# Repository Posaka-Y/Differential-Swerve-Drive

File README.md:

# Differential Swerve Drive

差動ステアユニット3基で構成する移動機構の、機構・制御・基板・ファームウェアをまとめた開発リポジトリです。

各ユニットはM3508+C620を2組とAMT222A-Vを持ち、ユニット内で差動の操舵・駆動制御を完結します。中央Teensy 4.1が3ユニットを協調制御し、mini PCはUSB-CDC経由でGUI・ログ・キャリブレーション操作を担います。

## 現在の構成

```text
mini PC (GUI / log)
  | USB-CDC
Teensy 4.1 (中央制御・安全I/O)
  |-- CAN1: 差動ステアユニット x3
  |     `-- STM32G474RET6 + C620 x2 + M3508 x2 + AMT222A-V
  |
  `-- CAN3: オドメトリ/IMUノード (unitId=4)
        `-- STM32F405RGT6 + AMT102 x3 + ICM-42688-P
```

- 中央CANとユニット内C620 CANは、いずれもClassic CAN 1 Mbpsの別バス。
- 制御系は中央の24V→5V降圧から`COMM_A / COMM_B / +5V / GND`で分配し、各基板で3.3Vを生成する。
- 確定事項の唯一の正本は[docs/ARCHITECTURE_DECISIONS.md](docs/ARCHITECTURE_DECISIONS.md)。

## まず読むもの

| 目的 | 文書 |
|---|---|
| 文書全体の案内 | [docs/PROJECT_DOCUMENT_INDEX.md](docs/PROJECT_DOCUMENT_INDEX.md) |
| 現在地・次の作業 | [PROGRESS.md](PROGRESS.md) |
| 設計上の確定事項 | [docs/ARCHITECTURE_DECISIONS.md](docs/ARCHITECTURE_DECISIONS.md) |
| 全体構成と責務 | [docs/SYSTEM_ARCHITECTURE.md](docs/SYSTEM_ARCHITECTURE.md) |
| ユニット基板・中央基板・オドメトリ基板 | [docs/electrical/](docs/electrical/) |
| 制御・運動学 | [docs/control/](docs/control/) |
| CAN・ネット名・メッセージ | [docs/communication/COMMUNICATION_NAMING_AND_IDS.md](docs/communication/COMMUNICATION_NAMING_AND_IDS.md) |
| ファームウェア | [firmware/README.md](firmware/README.md) と [firmware/PROGRESS.md](firmware/PROGRESS.md) |
| KiCad基板設計 | [hardware/README.md](hardware/README.md) |

階層化済みの`docs/control/`、`docs/electrical/`、`docs/communication/`などが更新対象です。`docs/`直下の旧メモは履歴として保存しており、更新対象ではありません。

## よく使うコマンド

リポジトリルートで実行します。

```powershell
# STM32G474 ファームウェア
.\firmware\scripts\build.ps1
.\firmware\scripts\flash.ps1

# KiCad設計のERC・PDF・DRC確認
.\tools\kicad\check.ps1
```

ファームウェア用ツールチェーンはスクリプトが自動検出します。パスに日本語を含むため、ビルド系スクリプトでは絶対パスを`cmd.exe`経由で渡さず、相対パスを使います。

## リポジトリ構成

```text
docs/       設計仕様、設計判断、試験計画
firmware/   STM32G474向けファームウェアとベンチ検証記録
hardware/   KiCadプロジェクト、共通ライブラリ、参照回路
tools/      KiCad検証などの補助スクリプト
```

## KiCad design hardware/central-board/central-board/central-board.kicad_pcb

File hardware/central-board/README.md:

# Central board schematic

## Files

- `central-board.sch`: 責務別child sheetを並べたroot index。
- `modules/100-power.sch`: 5V入力、eFuse、star distribution。
- `modules/200-teensy.sch`: Teensy 4.1 socket、固定pin map、安全出力のdefault state。
- `modules/300-can.sch`: Sensor / Expansion / DriveのCAN 3系統。
- `modules/600-safety.sch`: 24V E-stop loop、contactor driver、絶縁監視、motor bus sense。
- `modules/700-monitoring.sch`: INA238と外付けKelvin shunt interface。
- `modules/800-expansion.sch`: I2C/UART/SPI/GPIO、rearm、test access。
- `../../tools/kicad/generate-central-board-modules.ps1`: root＋6 moduleの再生成script。
- `../../tools/kicad/generate-central-board-schematic.ps1`: module生成の入力になる詳細回路generator。通常は直接実行しない。
- `../../docs/electrical/CENTRAL_BOARD_SCHEMATIC_WITH_BOM.html`: オドメトリ／駆動module資料と同じA3横テンプレートのreview正本。
- `../../output/pdf/CENTRAL_BOARD_SCHEMATIC_WITH_BOM.pdf`: 1機能1ページの回路図＋注意点＋簡易BOM、全7ページ。

## 開き方

KiCad Schematic Editorから`central-board.sch`を直接開き、rootのsheet blockから担当moduleへ移動する。初回保存時にKiCadの現行`.kicad_sch`形式へ変換してよい。変換後は生成scriptによる上書きを止め、`.kicad_sch`と変換されたchild sheetsを正本へ切り替える。

## 現段階の使い方

人間reviewでは`CENTRAL_BOARD_SCHEMATIC_WITH_BOM.pdf`を先に使い、1機能ずつ信号の流れ、注意点、BOMを確認する。KiCad sheetはその結果を転記してERCするための下位資料であり、review PDFの代用にはしない。TPS259470、TCAN1051、INA238、LTV-847Sなどの正式pinはdatasheetとKiCad symbolの両方で最終照合する。

PCBへ進む前に次を行う。

1. generic symbolを正式なlibrary symbolへ置換し、pin typeとfootprintをdatasheetに対して照合する。
2. 図中`TBD`をすべて閉じる。特にeFuse UVLO/OVLO、24V input保護、contactor clamp、shunt sense source fuse。
3. `docs/electrical/CENTRAL_BOARD_SCHEMATIC_REFERENCE.md`の接続表とcross-checkする。
4. No Connect、PWR_FLAG、power pin typeを整理し、ERC 0件へ収束させる。

現時点のKiCad ERCはgeneric pin-explicit symbolとlegacy `.sch` labelのためacceptance判定に使用しない。PDF/netlist出力が可能なことまでは確認済みで、PCB開始条件は`.kicad_sch`化後のERC 0件である。

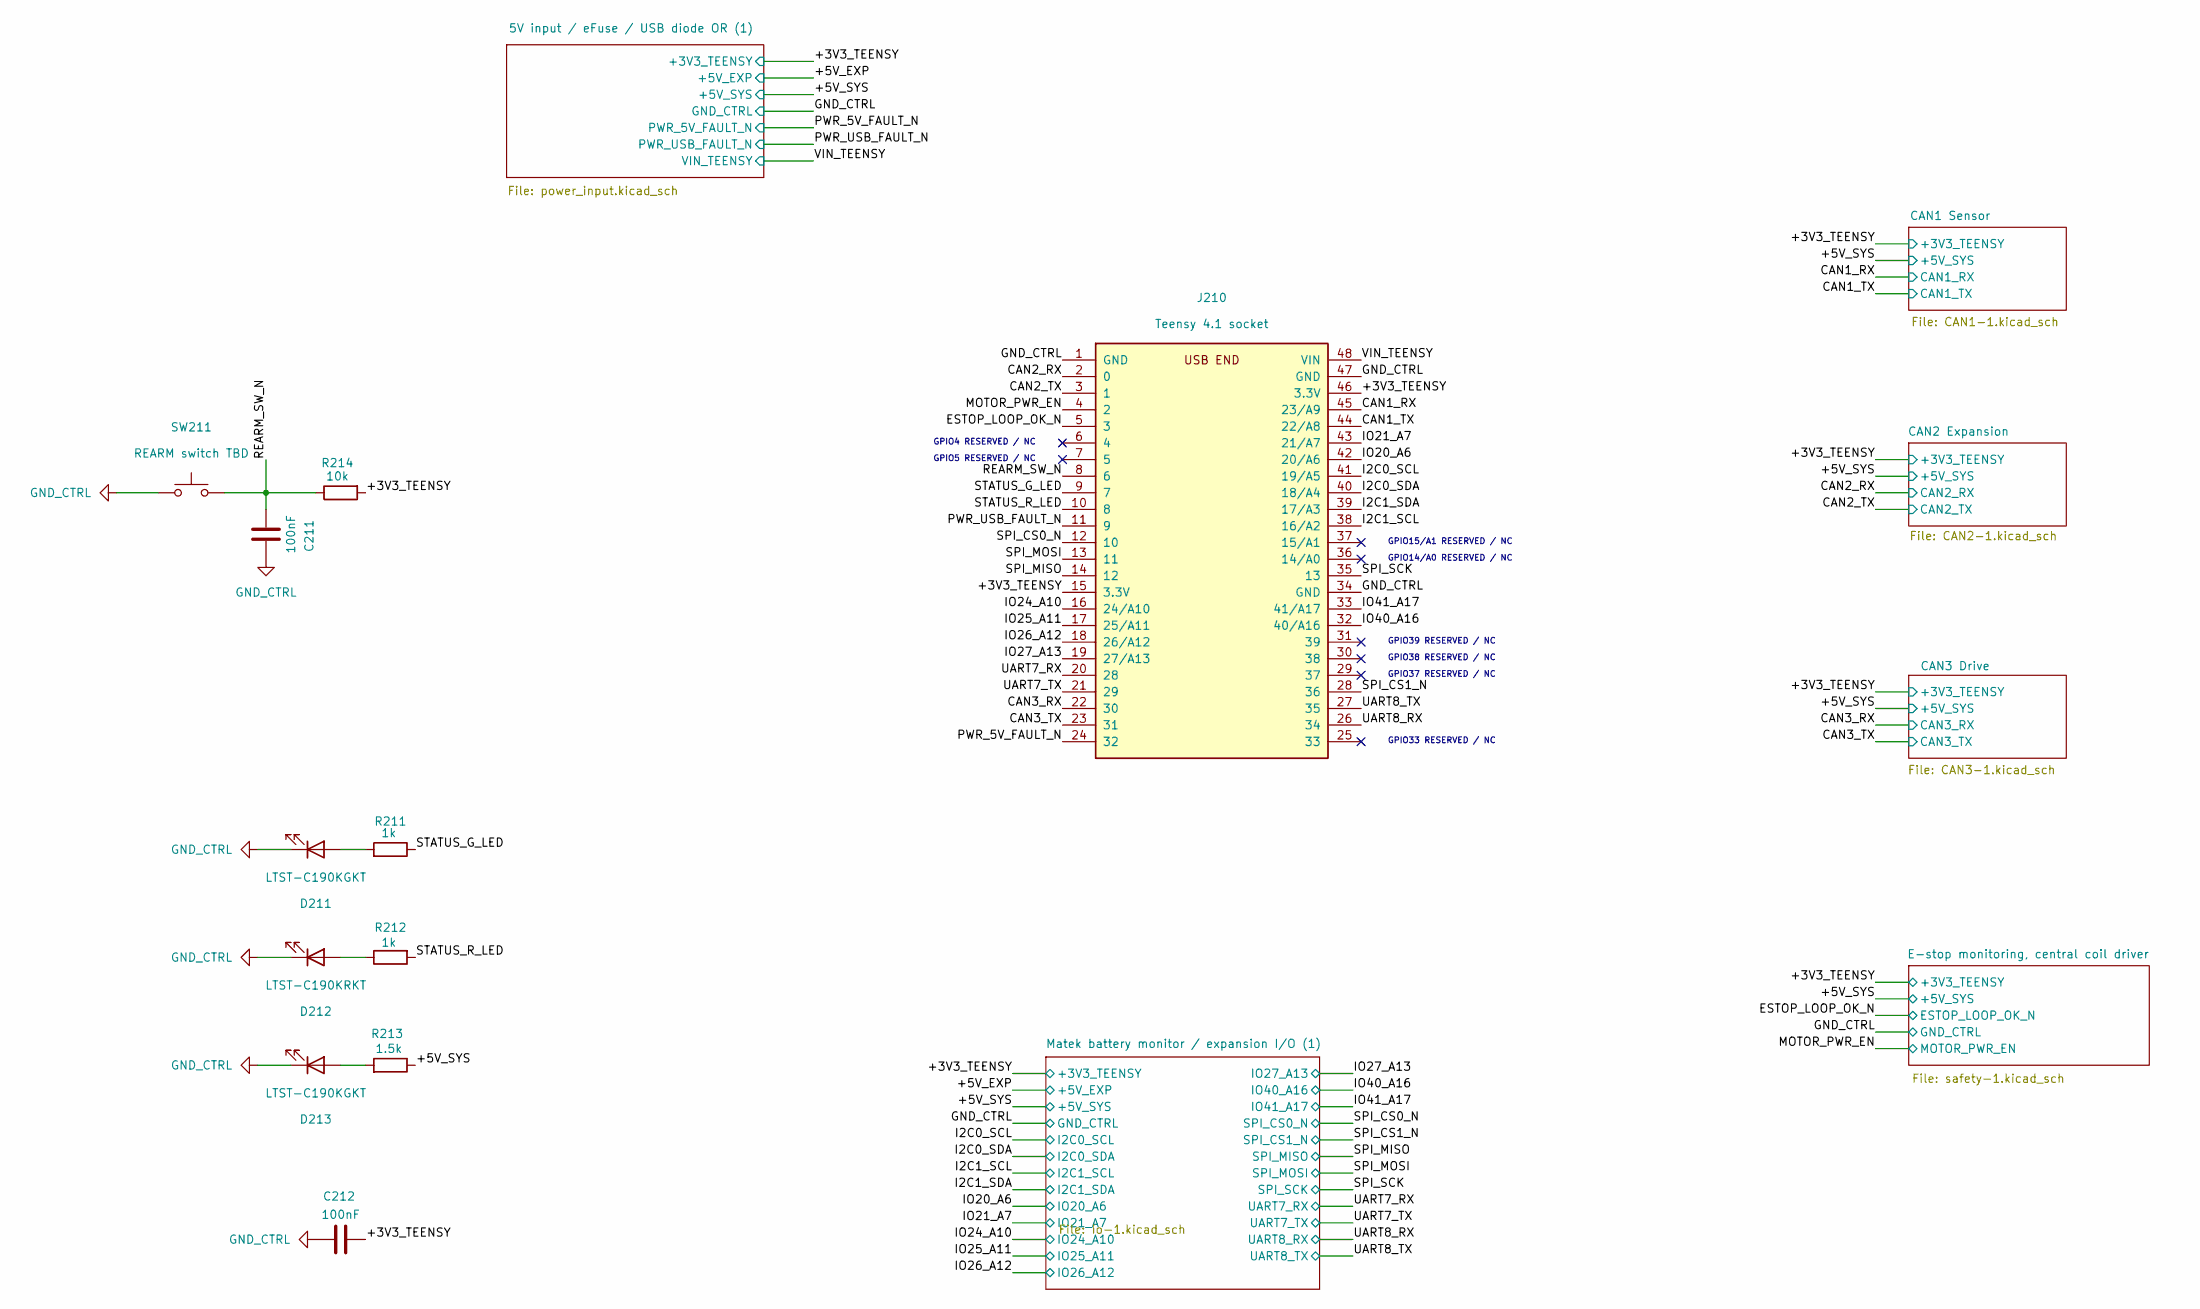
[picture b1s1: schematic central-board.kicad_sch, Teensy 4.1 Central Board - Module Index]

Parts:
C211, C212: 100nF; C_0603_1608Metric
D211, D213: LTST-C190KGKT; LED_0603_1608Metric
D212: LTST-C190KRKT; LED_0603_1608Metric
J210: Teensy 4.1 socket; Teensy41_Socket_2x24
R211, R212: 1k; R_0603_1608Metric
R213: 1.5k; R_0603_1608Metric
R214: 10k; R_0603_1608Metric
SW211: REARM switch TBD

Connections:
/+3V3_TEENSY: C212.1, J210.15 (3.3V), J210.46 (3.3V), R214.2; also elsewhere on the board
/+5V_SYS: R213.1; also elsewhere on the board
/CAN1_RX: J210.45 (23/A9); also elsewhere on the board
/CAN1_TX: J210.44 (22/A8); also elsewhere on the board
/CAN2_RX: J210.2 (0); also elsewhere on the board
/CAN2_TX: J210.3 (1); also elsewhere on the board
/CAN3_RX: J210.22 (30); also elsewhere on the board
/CAN3_TX: J210.23 (31); also elsewhere on the board
/ESTOP_LOOP_OK_N: J210.5 (3); also elsewhere on the board
/I2C0_SCL: J210.41 (19/A5); also elsewhere on the board
/I2C0_SDA: J210.40 (18/A4); also elsewhere on the board
/I2C1_SCL: J210.38 (16/A2); also elsewhere on the board
/I2C1_SDA: J210.39 (17/A3); also elsewhere on the board
/IO20_A6: J210.42 (20/A6); also elsewhere on the board
/IO21_A7: J210.43 (21/A7); also elsewhere on the board
/IO24_A10: J210.16 (24/A10); also elsewhere on the board
/IO25_A11: J210.17 (25/A11); also elsewhere on the board
/IO26_A12: J210.18 (26/A12); also elsewhere on the board
/IO27_A13: J210.19 (27/A13); also elsewhere on the board
/IO40_A16: J210.32 (40/A16); also elsewhere on the board
/IO41_A17: J210.33 (41/A17); also elsewhere on the board
/MOTOR_PWR_EN: J210.4 (2); also elsewhere on the board
/PWR_5V_FAULT_N: J210.24 (32); also elsewhere on the board
/PWR_USB_FAULT_N: J210.11 (9); also elsewhere on the board
/REARM_SW_N: C211.1, J210.8 (6), R214.1, SW211.1
/SPI_CS0_N: J210.12 (10); also elsewhere on the board
/SPI_CS1_N: J210.28 (36); also elsewhere on the board
/SPI_MISO: J210.14 (12); also elsewhere on the board
/SPI_MOSI: J210.13 (11); also elsewhere on the board
/SPI_SCK: J210.35 (13); also elsewhere on the board
/STATUS_G_LED: J210.9 (7), R211.1
/STATUS_R_LED: J210.10 (8), R212.2
/UART7_RX: J210.20 (28); also elsewhere on the board
/UART7_TX: J210.21 (29); also elsewhere on the board
/UART8_RX: J210.26 (34); also elsewhere on the board
/UART8_TX: J210.27 (35); also elsewhere on the board
/VIN_TEENSY: J210.48 (VIN); also elsewhere on the board
GND_CTRL: C211.2, C212.2, D211.1 (K), D212.1 (K), D213.1 (K), J210.1 (GND), J210.34 (GND), J210.47 (GND), SW211.2; also elsewhere on the board
unnamed: D211.2 (A), R211.2
unnamed: D212.2 (A), R212.1
unnamed: D213.2 (A), R213.2

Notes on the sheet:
GPIO38 RESERVED / NC
GPIO15/A1 RESERVED / NC
GPIO39 RESERVED / NC
GPIO14/A0 RESERVED / NC
GPIO33 RESERVED / NC
GPIO5 RESERVED / NC
GPIO37 RESERVED / NC
GPIO4 RESERVED / NC

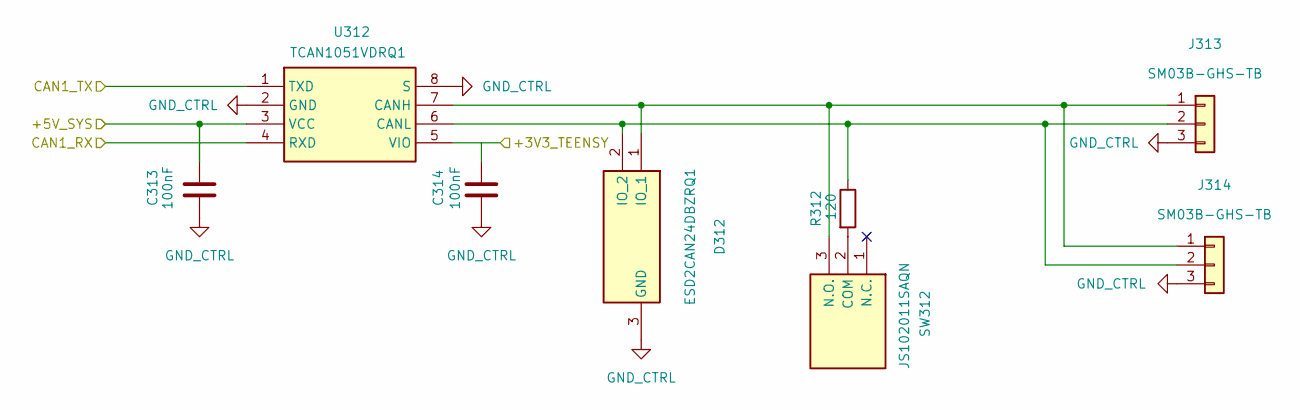
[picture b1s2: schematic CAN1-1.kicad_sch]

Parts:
C313, C314: 100nF; C_0603_1608Metric
D312: ESD2CAN24DBZRQ1; SOT-23
J313, J314: SM03B-GHS-TB; JST_GH_SM03B-GHS-TB_1x03-1MP_P1.25mm_Horizontal
R312: 120; R_0603_1608Metric
SW312: JS102011SAQN
U312: TCAN1051VDRQ1; SOIC-8_3.9x4.9mm_P1.27mm

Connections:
/+3V3_TEENSY: C314.1, U312.5 (VIO); also elsewhere on the board
/+5V_SYS: C313.1, U312.3 (VCC); also elsewhere on the board
/CAN1_RX: U312.4 (RXD); also elsewhere on the board
/CAN1_TX: U312.1 (TXD); also elsewhere on the board
GND_CTRL: C313.2, C314.2, D312.3 (GND), J313.3, J314.3, U312.2 (GND), U312.8 (S); also elsewhere on the board
unnamed: D312.1 (IO_1), J313.1, J314.1, SW312.3 (N.O.), U312.7 (CANH)
unnamed: D312.2 (IO_2), J313.2, J314.2, R312.1, U312.6 (CANL)
unnamed: R312.2, SW312.2 (COM)

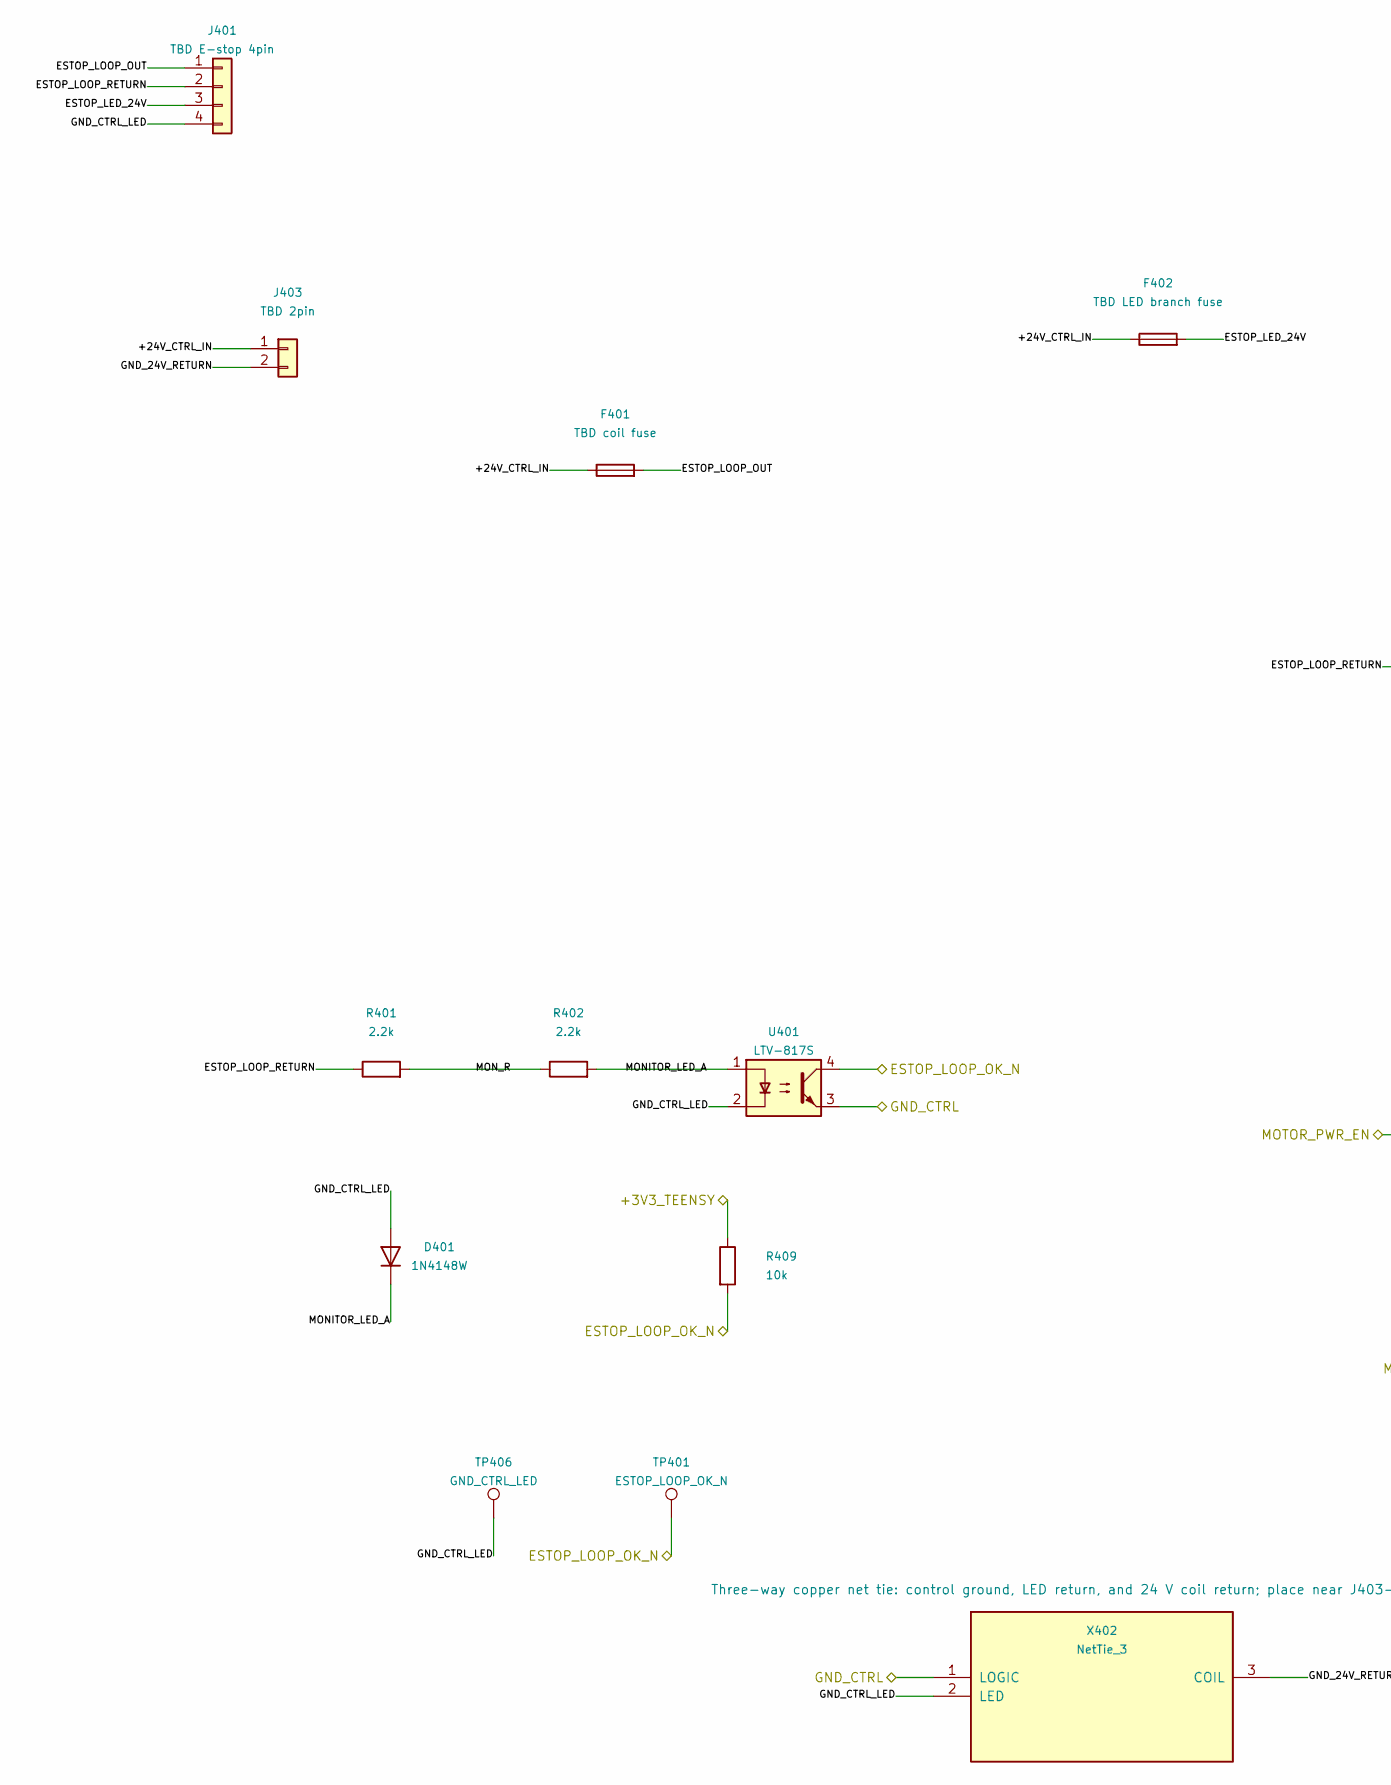
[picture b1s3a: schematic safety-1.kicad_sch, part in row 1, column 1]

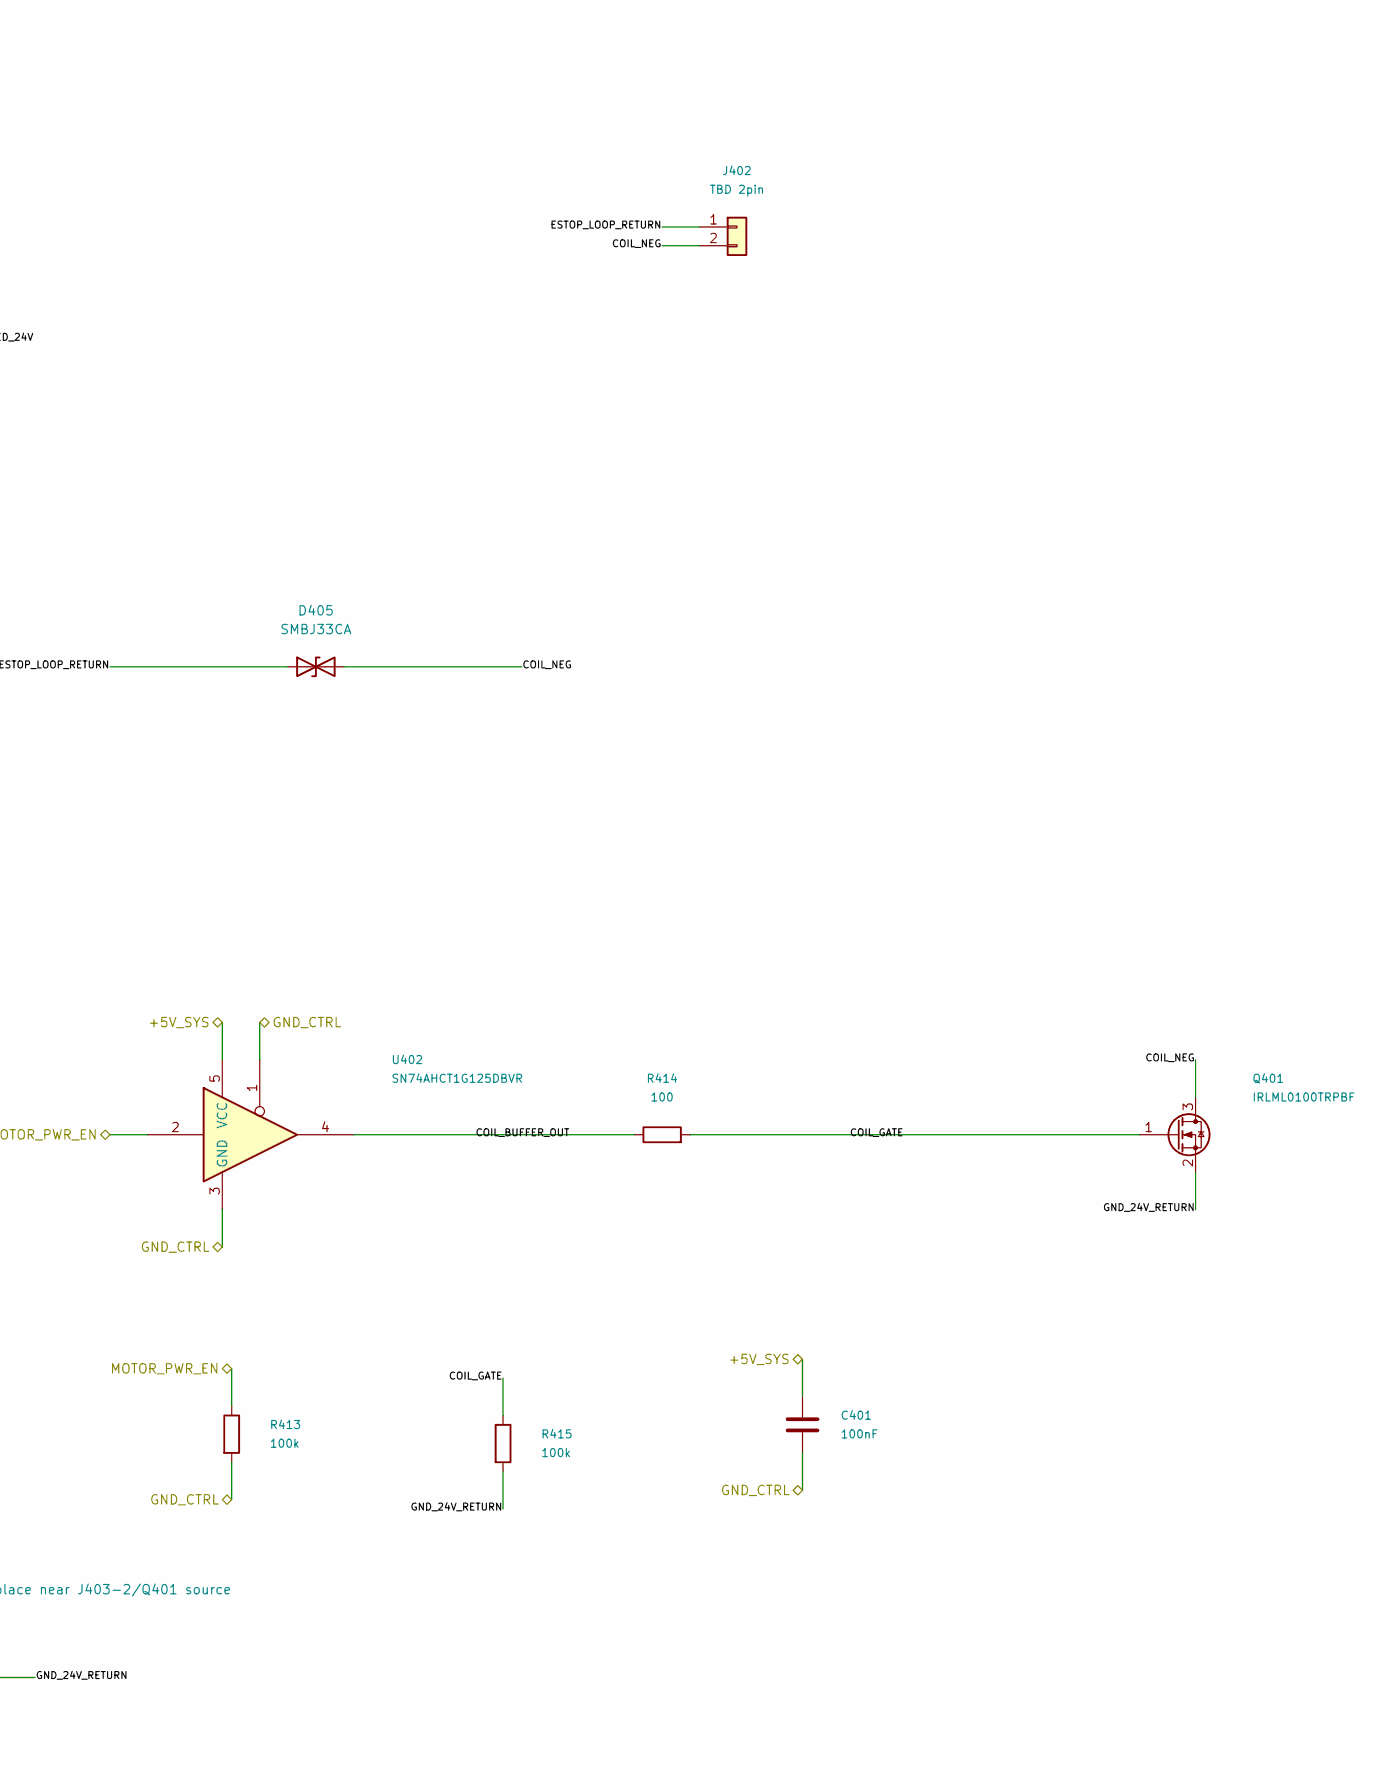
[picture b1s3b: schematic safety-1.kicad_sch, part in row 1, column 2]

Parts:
C401: 100nF; C_0603_1608Metric
D401: 1N4148W; D_SOD-123
D405: SMBJ33CA; D_SMB; MPN SMBJ33CA
F401: TBD coil fuse
F402: TBD LED branch fuse
J401: TBD E-stop 4pin; JST_XH_S4B-XH-A_1x04_P2.50mm_Horizontal
J402: TBD 2pin
J403: TBD 2pin; JST_XH_S2B-XH-A_1x02_P2.50mm_Horizontal
Q401: IRLML0100TRPBF; SOT-23
R401, R402: 2.2k; R_0603_1608Metric
R409: 10k; R_0603_1608Metric
R413, R415: 100k; R_0603_1608Metric
R414: 100; R_0603_1608Metric
TP401: ESTOP_LOOP_OK_N; TestPoint_Pad_D1.5mm
TP406: GND_CTRL_LED; TestPoint_Pad_D1.5mm
U401: LTV-817S; SMDIP-4_W9.53mm
U402: SN74AHCT1G125DBVR; SOT-23-5
X402: NetTie_3; NetTie-3_SMD_Pad2.0mm

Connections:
/+3V3_TEENSY: R409.1; also elsewhere on the board
/+5V_SYS: C401.1, U402.5 (VCC); also elsewhere on the board
/E-stop monitoring, central coil driver/+24V_CTRL_IN: F401.1, F402.1, J403.1
/E-stop monitoring, central coil driver/COIL_BUFFER_OUT: R414.1, U402.4
/E-stop monitoring, central coil driver/COIL_GATE: Q401.1 (G), R414.2, R415.1
/E-stop monitoring, central coil driver/COIL_NEG: D405.2 (A2), J402.2, Q401.3 (D)
/E-stop monitoring, central coil driver/ESTOP_LED_24V: F402.2, J401.3
/E-stop monitoring, central coil driver/ESTOP_LOOP_OUT: F401.2, J401.1
/E-stop monitoring, central coil driver/ESTOP_LOOP_RETURN: D405.1 (A1), J401.2, J402.1, R401.1
/E-stop monitoring, central coil driver/GND_24V_RETURN: J403.2, Q401.2 (S), R415.2, X402.3 (COIL)
/E-stop monitoring, central coil driver/GND_CTRL_LED: D401.2 (A), J401.4, TP406.1 (1_1), U401.2, X402.2 (LED)
/E-stop monitoring, central coil driver/MONITOR_LED_A: D401.1 (K), R402.2, U401.1
/E-stop monitoring, central coil driver/MON_R: R401.2, R402.1
/ESTOP_LOOP_OK_N: R409.2, TP401.1 (1_1), U401.4; also elsewhere on the board
/MOTOR_PWR_EN: R413.1, U402.2; also elsewhere on the board
GND_CTRL: C401.2, R413.2, U401.3, U402.1, U402.3 (GND), X402.1 (LOGIC); also elsewhere on the board
